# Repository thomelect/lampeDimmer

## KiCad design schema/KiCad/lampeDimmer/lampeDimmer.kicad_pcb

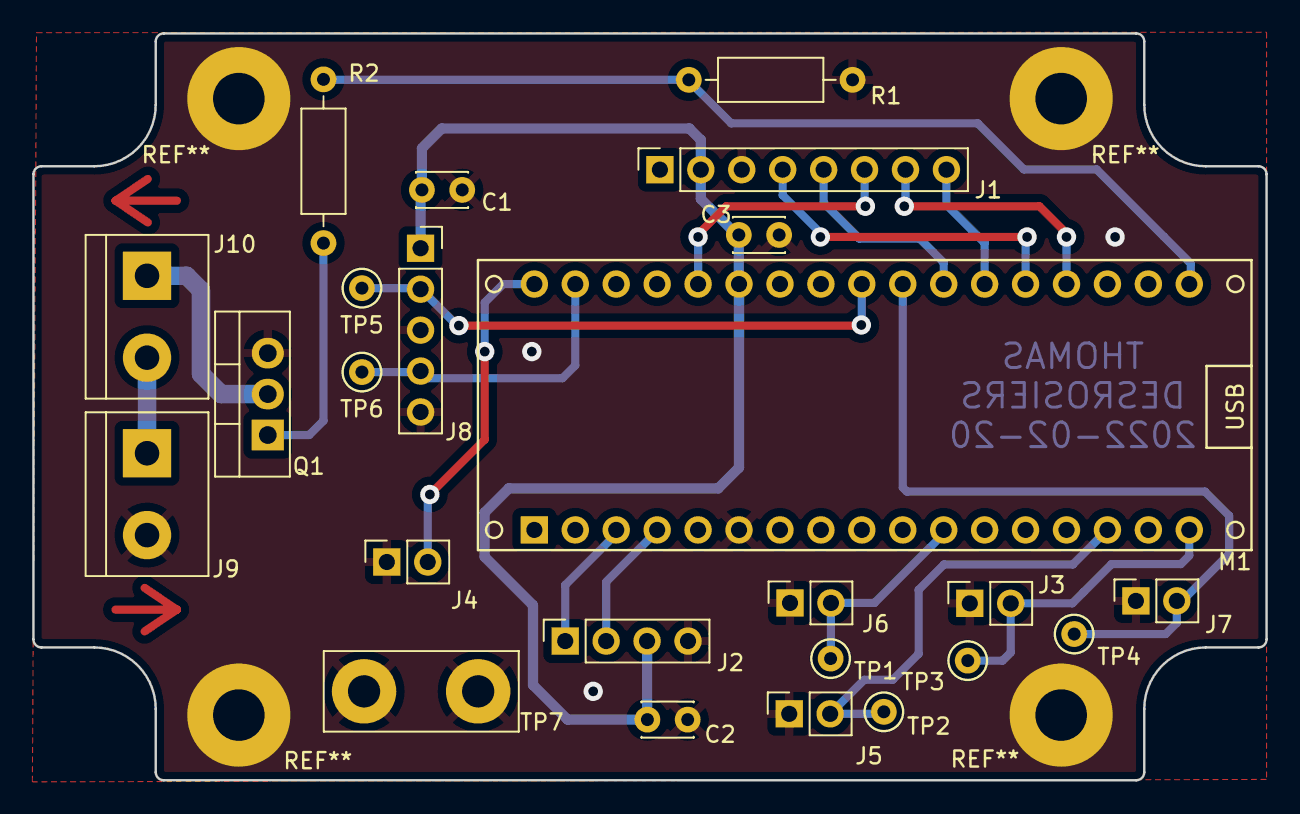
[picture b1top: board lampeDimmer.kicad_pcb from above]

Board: 2 copper layers, 76.5 x 46.3 mm, 24 parts (0 on the bottom side), 20 nets.

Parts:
C1, C2, C3: 100nF; C_Disc_D3.0mm_W2.0mm_P2.50mm
J1: PICkit4; PinSocket_1x08_P2.54mm_Vertical
J2: USART; PinSocket_1x04_P2.54mm_Vertical
J3: EXT_IO-1; PinSocket_1x02_P2.54mm_Vertical
J4: SW_ON-OFF; PinSocket_1x02_P2.54mm_Vertical
J5: EXT_PWM4B; PinSocket_1x02_P2.54mm_Vertical
J6: EXT_PWM4D; PinSocket_1x02_P2.54mm_Vertical
J7: EXT_ADC1; PinSocket_1x02_P2.54mm_Vertical
J8: CON_POT_SW; PinSocket_1x05_P2.54mm_Vertical
J9: Entrée; TerminalBlock_bornier-2_P5.08mm
J10: Sortie; TerminalBlock_bornier-2_P5.08mm
M1: ARDUINO_MICRO; Arduino_Micro
Q1: FQP13N06L; TO-220-3_Vertical
R1: 100; R_Axial_DIN0207_L6.3mm_D2.5mm_P10.16mm_Horizontal
R2: 1k; R_Axial_DIN0207_L6.3mm_D2.5mm_P10.16mm_Horizontal
TP1, TP2, TP3, TP4, TP5, TP6: TestPoint; TestPoint_Keystone_5000-5004_Miniature-Resistor
TP7: TestPoint_2Pole; TestPoint_Bridge_Pitch7.08mm_Drill2.0mm

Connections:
+5V: C1.1, C2.1, C3.1, J1.2 (VDD), J2.3 (VCC), J8.1, M1.29 (5V)
+24V: J9.1, J10.2
/EXT_ADC1: J7.2, M1.25 (PF1(ADC1)), TP4.1
/EXT_IO-1: J3.2, M1.17 (PD6(ADC9/#OC4D)), TP3.1
/EXT_OC4B: J5.2, M1.15 (PB6(ADC13/OC1B/OC4B/PCINT6)), TP2.1
/EXT_OC4D: J6.2, M1.11 (PD7(ADC10/OC4D)), TP1.1
/POT_ADC: J8.2, M1.26 (PF0(ADC0)), TP5.1
/SORTIE: J10.1, Q1.2 (D)
/SW_ON-OFF: J4.2, M1.34 (PB1(SCLK))
/SW_VEILLE: J8.4, M1.33 (PB3(MISO)), TP6.1
GND: C1.2, C2.2, C3.2, J1.3 (GND), J2.4 (GND), J3.1, J4.1, J5.1, J6.1, J7.1, J8.3, J8.5, J9.2, M1.6 (GND), Q1.3 (S), R1.2, TP7.1, TP7.2
unnamed: J1.4 (TDO), M1.22 (PF6(TDO))
unnamed: J1.5 (TCK), M1.24 (PF4(TCK))
unnamed: J1.6 (#RESET), M1.30 (RESET)
unnamed: J1.7 (TDI), M1.21 (PF7(TDI))
unnamed: J1.8 (TMS), M1.23 (PF5(TMS))
unnamed: J2.1 (TX), M1.3 (PD3(TX))
unnamed: J2.2 (RX), M1.4 (PD2(RX))
unnamed: M1.18 (PC7(OC4A)), R1.1, R2.1
unnamed: Q1.1 (G), R2.2

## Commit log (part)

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2021-08-12 Innitial Commit
2021-08-12 Ajout de documentation de fonction de la librairie ADC.
2021-08-12 Conversion des fichiers en UTF-8 BOM
2021-08-13 Ajout d'une liste OneNote de choses à faire
2021-08-14 Retrait des éléments qui causait problème. [Fonctionnel comme avant!]
2021-08-14 Ajout d'un objectif
2021-08-14 [GUI] -Correction ComboBox -> le mode choisi est appliqué des que l'utilisateur clique dessus, plus besoins de cliquer sur un autre mode avant de revenir au mode précédent.
2021-08-15 [GUI] Le bouton n'affiche plus de texte mais bien une image d'une ampoule allumée ou éteinte.
2021-08-15 [GUI] + [CODE] -Ajout d'un mode veille (luminosité minimale) lorsque l'interrupteur est en position OFF.
    Ajout d'une copie du code, pour une version utilisant la communication par USB
2022-01-05 + Ajout d'un fichier d'exclusion git (.gitignore).
2022-01-05 + ajout d'un barre de status et d'une valeur initiale de 0%.
2022-01-06 'Merge' .gitignore depuis master.
2022-01-06 Envoie de la nouvelle valeur sur changement seulement.
2022-01-06 + Ajout d'un bouton pour le GET_ETAT. + La fonction sendSerialData() est utilisée pour l'envoie de toute les commandes.
2022-01-06 + Ajout d'une fonction séparée pour les commandes TX pour éviter les boucles infinies.
    indentation.
2022-01-06 + Ajout d'un retour de la valeur actuelle quand le système est en veille.
2022-01-07 On feature-GUI: + Ajout d'une fonctionnalité d'acquisition de la valeur de l'ADC à la connection au port série. -> FONCTIONNELLE.
2022-01-07 + Ajout d'une fonctionnalitée qui permet de sélectionner automatiquement dans les comboBox le valeur définie dans les defines.
2022-01-07 + Ajout d'un menu "Configuration" et d'une interface pour les réglages de l'interface (en cours).
2022-01-07 + Ajout de l'envoie de la valeur actuelle (nouveau case).
2022-01-07 + Ajout d'un case pour retourner à la fois la valeur du pot et la valeur actuelle. ~ Modification des cases.
2022-01-07 ~ Mise à jours de la documentation. - Suppression de code inutile.
2022-01-07 + Ajout des deux différents cases pour la réception des états.
2022-01-07 + Ajout d'une fonctionnalitée pour récupérer le mode de veille actuel. -> NON-FONCTIONNEL.
2022-01-07 ! Fonctionnalitée pour récupérer le mode de veille actuel. -> FONCTIONNEL. + Ajout et mise en forme de l'affichage dans la console.
2022-01-07 !! Version USB fonctionnel **sauf l'acquisition du mode veille**
2022-01-07 + Petit ajout: si le port par défaut n'est pas trouvé, le premier dans la liste est affiché.
2022-01-08 + Ajout d'un case INIT pour récupérer les valeurs initiales.
2022-01-08 ! Problème réglé
2022-01-08 - Suppression des cases non utilisés. -> TERMINÉ GUI FONCTIONNE COMME PRÉVU!
2022-01-08 _ Mise à jours effectuée. _ Code fonctionnel.
2022-01-12 + Ajout de code pour faire une connexion automatique au port série.
    !! FONCTIONNEL !!
2022-01-12 + Ajout d'une classe pour la lecture et l,écriture dans le fichier. - EN COURS -
2022-01-12 + Ajout d'un bouton pour tester la fonction saveToFile().
    ! fonction saveToFile - FONCTIONNELLE !
2022-01-12 !! Connexion automatique fonctionnelle en fonction du fichier du configuration. !!
2022-01-13 !! Fonctionnalitée de connexion automatique - FONCTIONNELLE.
2022-01-13 + Ajout d'un getter pour récupérer les informations du port pour les afficher dans la statusBar. ~ Les boutons sont désactivés lorsqu'aucun port n'est connecté. ~ Les boutons sont activés seulement l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
2022-01-13 ~ Modification des valeurs retournés pour l'état initial. La valeur actuelle de la sortie est maintenant retournée.
2022-01-16 + Ajout d'un QSystemTrayIcon. - EN COURS -
2022-01-16 + Récupération du dernier mode veille.
2022-01-16 ~ Correction erreur switchcase Tx.
2022-01-16 + Fonction d'envoie du mode actuel. - EN COURS -
2022-01-16 + Ajout du nouveau case d'envoi. + Envoi du mode lors de la demande des valeurs initiales. - EN COURS -
2022-01-16 + Ajout de l'affichage du mode veille dans la statusBar lorsque le système est en veille. + Ajout de commentaires. + Utilisation de boutonManage dans execRxCommand afin de simplifier le code.
2022-01-21 ~ Régler le problème du slider et dial qui ne sont pas glissables. ~ Régler le problème des dernières reçues qui ne sont pas toujours prises en compte.
2022-01-21 + Ajout de la gestion de la valeur du potentiomètre lors de la réception des valeurs initiales.
2022-01-21 + Ajout sauvegarde de la valeur custom dans le fichier .ini. ~ Modification de la condition pour afficher la spinBox seulement quand le mode veille est "CUSTOM". + Ajout de l'envoie de la valeur cust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
2022-01-21 + Ajout de la gestion de la valeur de sortie custom en mode veille.
2022-01-22 + Ajout d'une enum pour remplacer la variable qui contient l'état du mode veille. + Ajout d'info de débogage. ~ La position et valeur affichée sont maintenant de 0 en mode veille.
2022-01-22 + Ajout d'une condition permettant de supprimer le fichier si sa date de création > que celle spécifiée par le define. + Utilisation de QFileInfo pour récupérer les infos du fichier. +Ajout d'une exc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
2022-01-24 + Ajout d'une recherche avec les defines dans setupserialdialog.h. Si aucune correspondance avec les les valeurs dans le .ini sont trouvés, une recherche est faites avec les defines. Si il n'y a touj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
2022-02-21 + Ajout des schéma et PCB sous KiCad.
2022-02-26 + Ajout des fichiers gerber. + Ajout d'un fichier pdf du schéma. - Suppression du schéma sous Multisim.
2022-02-28 + Ajout des cartouches dans le dossier du projet.
2022-03-05 + Mise à jours du port sur lequel se trouve l'interrupteur du potentiomètre (PB1 -> PB3).
2022-03-15 - Suppression dossier inutile dans le dossier schéma.
2022-06-25 Mise à jour .gitignore.
2022-06-25 * Les titres des paramètres dans settings-
2022-12-07 * Mise à jour de l'entête. * Ordre des déclarations de fonctions modifié.
2022-12-08 + Ajout de documentation des fonction recepTimer et readSerialData dans le but d'expliquer leur utilité et leurs fonctionnement.
2022-12-09 **# [TRANSMISSION]** + Ajout d'un timer, d'un état de transmission dans TX_COMMANDES et de la fonction temperatureAck(); * Ces éléments seront utilisées afin d'envoyer une demande de retour de la val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
    **# [RÉCEPTION]**
    * À venir...
2022-12-09 **# [RÉCEPTION/TRANSMISSION]** + Ajout d'un état de transmission dans RX_COMMANDES, et de réception dans TX_COMMANDES pour les états de température. + Le code et le librairies (sa structure en généra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
2022-12-10 **# [AFFICHAGE]** + Ajout d'un label pour afficher la température dans l'interface.
2022-12-10 + Ajout de la librairie eeprom.h qui est utilisé afin d'écrire dans la mémoire eeprom la valeur du monde de veille. Ainsi, cette valeur n'est pas perdue dans l'éventualité au l'alimentation du arduin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
2022-12-11 **# [MENU]** + Ajout d'une option dans le menu Outils appelé *Préférences* qui éventuellement ouvrira une fenêtre pour configurer différentes options. *[EN_COURS...]*
2022-12-12 **# [MENU]** + Ajout d'un deuxième onglet de menu appalé *Fichier* qui contient l'option *Quitter* et contiendra les option principales *(Quitter, préférences, etc...)* * Le menu *Outils* contient qu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
2022-12-12 ***Application des ajout de la branche thomas/feature-GUI-autoON à cette branche puisque cette branche se concentre sur la feature du menu de préférences et thomas/feature-GUI-autoON se concentre sur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
2022-12-13 # [PRÉFÉRENCES] * Modification du *layout* de test. + Ajout de la classe QSettings et création d'un objet de cette même classe appelé *settingsPref*. Ainsi, l'état de check box et des liste déroulant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
2022-12-13 # [PRÉFÉRENCES] ***[DÉMARRAGE]*** * Le comportement lors du démarrage et de l'arrêt est maintenant déterminé par la valeur du check box dans le menu préférences. - Retrait des ifdefine dans le main.c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
2022-12-13 # [PRÉFÉRENCES] + Ajout de la liste déroullante de sélection du mode de veille dan la fenêtre préférence. + Ajout de titres. [FONCTIONNEL]
2022-12-14 * Correction d'un problème qui faisant en sorte qu'une modification de l'option qui empêche de quitter l'application ne pouvait pas être appliquée en redémarrant l'application. [FONCTIONNEL]
2022-12-17 # [REDÉMARRAGE] - Retrait du bouton de redémarrage de l'écran principal. (il est seulement dans l'écran de préférences.) - Retrait de la fonction de redémarrage dans mainwindow.c.h. + Ajout de la fon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
2022-12-18 # [DÉMARRAGE-AUTO] + Ajout d'un fonction dans setuppreference.h qui écrit dans le registre dans → *HKEY_CURRENT_USER\Software\Microsoft\Windows\CurrentVersion\Run* l'emplacement de l'exécutable de l'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
2022-12-19 # [ICON BARRE DE TÂCHE - MENU]
    + Ajout d'options fictives dans le menu qui est rendu visible lors d'un click droit sur l'icon dans la barre des tâches.
    *[FONCTIONNEL]*
2022-12-20 + Ajout d'une fonction appelée toggleLampe() qui est appelée lorsque qu'on veut mettre à On ou Off la lumières. * Cette fonction contient ce qui se trouvait au paravant dans la fonction on_pushBotton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
    *[FONCTIONNEL]*
2022-12-20 * Nettoyage du code.
2022-12-20 Modification de la hauteur du grid layout.
2022-12-21 # [ICON BARRE DE TÂCHE - MENU]
    + Attribution de nom représentatifs aux actions du menu du systemTray.
    + Connexion des actions du menu à des fonctions.
    * Modification de la fonction toggleLamp pour qu'elle puisse être appelée sans attribut.
    * Modification de la fonction *toggleLamp* → *toggleLumiere*.
    * Modification du texte de l'*action1* en fonction de la prochaine valeur après le click du même bouton.
    *[FONCTIONNEL]*
2022-12-22 # [ICON BARRE DE TÂCHE - MENU / SOUS-MENU]
    * Organisation de l'ordre des items du menu.
    * Ordre dans le code pour le menu et le sous menu.
    * Ajout de séparateurs dans le menu.
    *[FONCTIONNEL]*
2022-12-23 # [PRÉFÉRENCES] - Suppression d'options inutiles dans le menu de préférences.
    *[FONCTIONNEL]*
2022-12-24 # [BYPASS - VEILLE]
    + Ajout d'un case pour la réception pour *SET_BYPASS_VAL*
    + Ajout d'un flag pour le mode *bypassMode*.
    *[FONCTIONNEL]*
2022-12-24 # [BYPASS - VEILLE]
    + Ajout du retour de valeur.
    *[FONCTIONNEL]*
2022-12-24 # [BYPASS - VEILLE]
    + Début de l'ajout d'appels de la fonction *execTxCommand()* avec bypassMode.
    *[EN_COURS... / NON FONCTIONNEL]*
2022-12-24 # [EEPROM] + Ajout de la librairie eeprom.h qui est utilisé afin d'écrire dans la mémoire eeprom la valeur du monde de veille. * Ainsi, cette valeur n'est pas perdue dans l'éventualité au l'alimentat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
    Fix #2
    [TERMINÉ - FONCTIONNEL]
2022-12-25 # [DARK MODE]
    + Ajout de qDarkStyle au projet.
    + Application du style en fonction de la valeur du define DARK_MODE.
    * Pas encore 100% intégré.
    * Modification du .gitignore.
    #7
    *[EN COURS]*
2022-12-26 # [GUI UPGRADE]
    * Légère modification de la taille des layouts et de la fenêtre.
    #8
    *[FONCTIONNEL]*
